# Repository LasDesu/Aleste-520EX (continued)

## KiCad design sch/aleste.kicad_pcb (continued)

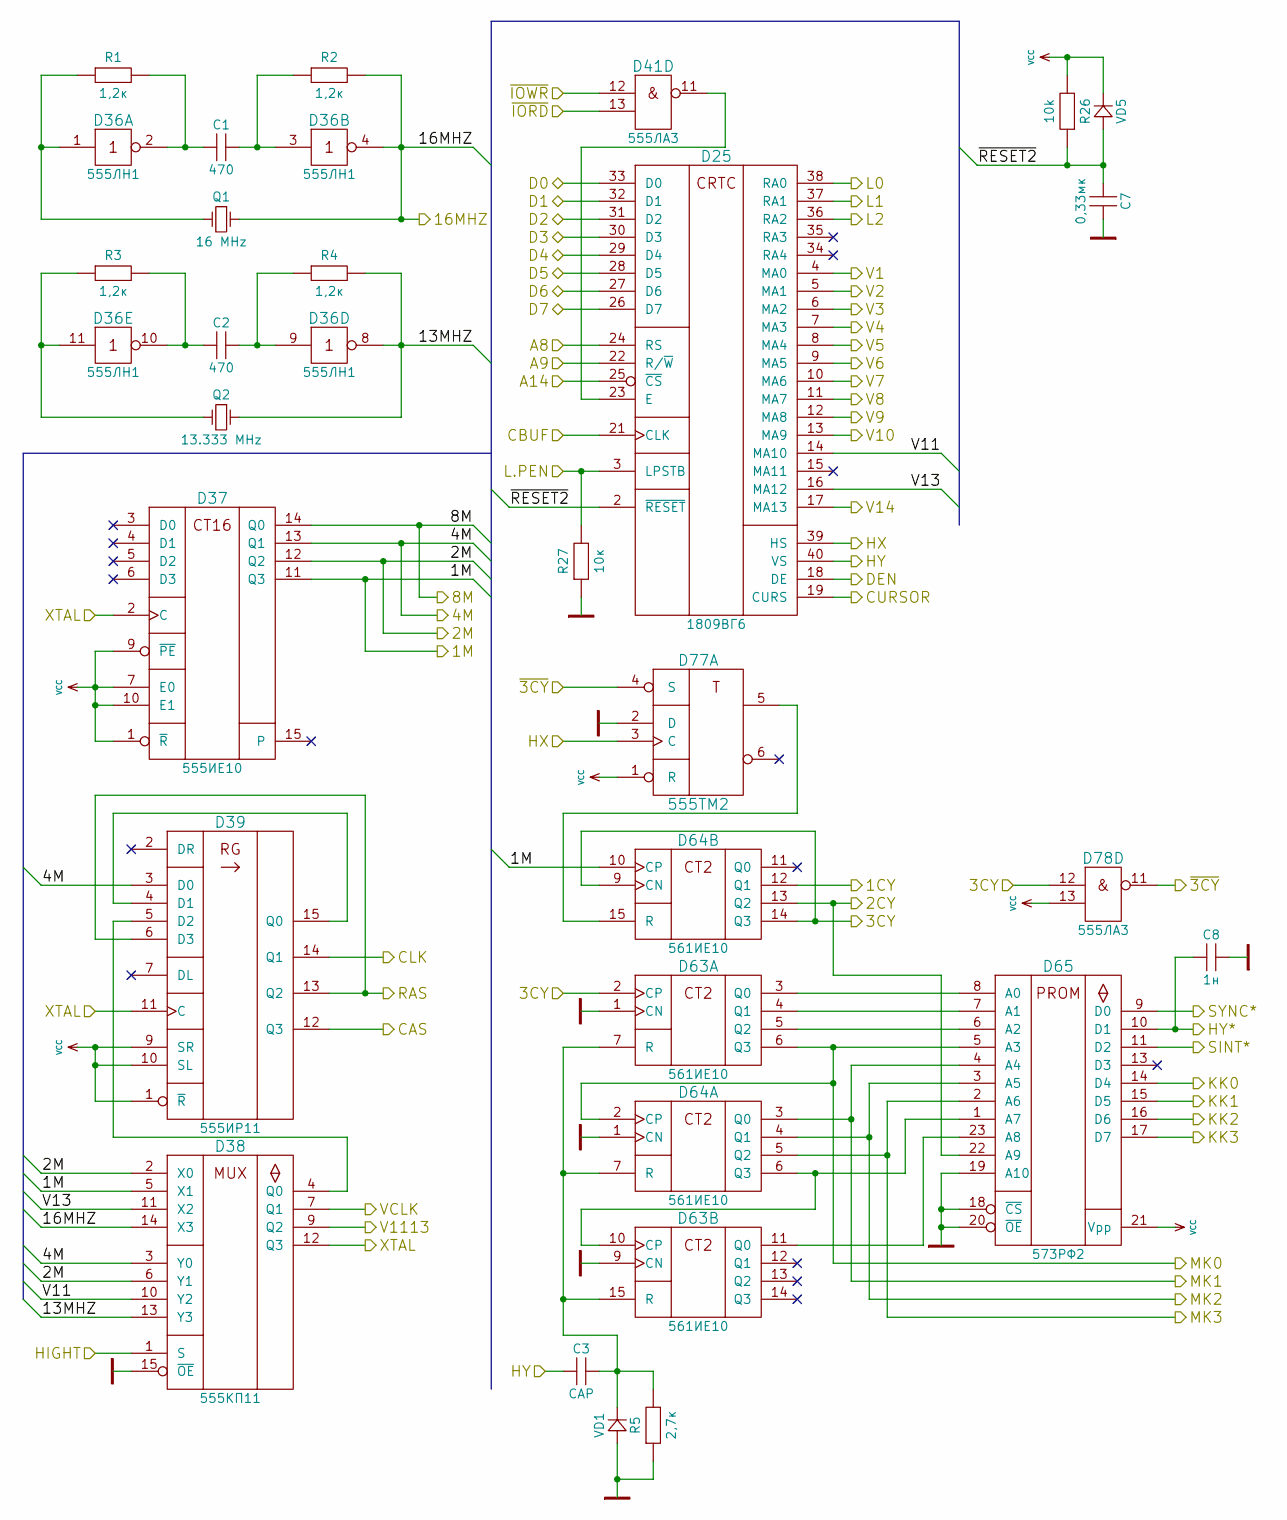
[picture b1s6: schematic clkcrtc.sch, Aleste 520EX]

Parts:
C1, C2: 470; C_Disc_D7.5_P2.5
C3: CAP; C_Disc_D7.5_P2.5
C7: 0,33мк; C_Disc_D7.5_P2.5
C8: 1н; C_Disc_D7.5_P2.5
D25: 1809ВГ6; DIP-40
D36: 555ЛН1; DIP-14
D37: 555ИЕ10; DIP-16
D38: 555КП11; DIP-16
D39: 555ИР11; DIP-16
D41, D78: 555ЛА3; DIP-14
D63, D64: 561ИЕ10; DIP-16
D65: 573РФ2; DIP-24
D77: 555ТМ2; DIP-14
Q1: 16 MHz; Crystal_HC49-U_Horizontal_Typ1
Q2: 13.333 MHz; Crystal_HC49-U_Horizontal_Typ1
R1, R2, R3, R4: 1,2к; Resistor_Horizontal_RM7.5mm
R5: 2,7к; Resistor_Horizontal_RM7.5mm
R26: 10k; Resistor_Horizontal_RM7.5mm
R27: 10к; Resistor_Horizontal_RM7.5mm
VD1, VD5: DIODE_MY; Diode_DO-35_SOD27_Horizontal_RM7.5

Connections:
/1CY: D64.12 (Q1); also elsewhere on the board
/1M: D37.11 (Q3), D38.5 (X1), D64.10 (CP); also elsewhere on the board
/2CY: D64.13 (Q2), D65.22 (A9); also elsewhere on the board
/2M: D37.12 (Q2), D38.2 (X0), D38.6 (Y1); also elsewhere on the board
/3CY: D63.2 (CP), D64.9 (CN), D64.14 (Q3), D78.12 (in1)
/4M: D37.13 (Q1), D38.3 (Y0), D39.3 (D0); also elsewhere on the board
/8M: D37.14 (Q0); also elsewhere on the board
/16MHZ: D36.4 (out), D38.14 (X3), Q1.1, R2.2; also elsewhere on the board
/A8: D25.24 (RS); also elsewhere on the board
/A9: D25.22 (R/~W); also elsewhere on the board
/A14: D25.25 (~CS); also elsewhere on the board
/CAS: D39.12 (Q3); also elsewhere on the board
/CBUF: D25.21 (CLK); also elsewhere on the board
/CLK: D39.14 (Q1); also elsewhere on the board
/CURSOR: D25.19 (CURS); also elsewhere on the board
/Clocks & CRTC/13MHZ: D36.8 (out), D38.13 (Y3), Q2.1, R4.2
/Clocks & CRTC/V11: D25.14 (MA10), D38.10 (Y2)
/Clocks & CRTC/V13: D25.16 (MA12), D38.11 (X2)
/Clocks & CRTC/~RESET2: C7.2, D25.2 (~RESET), R26.1, VD5.2
/D0: D25.33 (D0); also elsewhere on the board
/D1: D25.32 (D1); also elsewhere on the board
/D2: D25.31 (D2); also elsewhere on the board
/D3: D25.30 (D3); also elsewhere on the board
/D4: D25.29 (D4); also elsewhere on the board
/D5: D25.28 (D5); also elsewhere on the board
/D6: D25.27 (D6); also elsewhere on the board
/D7: D25.26 (D7); also elsewhere on the board
/DEN: D25.18 (DE); also elsewhere on the board
/HIGHT: D38.1 (S); also elsewhere on the board
/HX: D25.39 (HS), D77.3 (C); also elsewhere on the board
/HY: C3.1, D25.40 (VS); also elsewhere on the board
/HY*: C8.1, D65.10 (D1); also elsewhere on the board
/KK0: D65.14 (D4); also elsewhere on the board
/KK1: D65.15 (D5); also elsewhere on the board
/KK2: D65.16 (D6); also elsewhere on the board
/KK3: D65.17 (D7); also elsewhere on the board
/L0: D25.38 (RA0); also elsewhere on the board
/L1: D25.37 (RA1); also elsewhere on the board
/L2: D25.36 (RA2); also elsewhere on the board
/L.PEN: D25.3 (LPSTB), R27.2; also elsewhere on the board
/MK0: D63.6 (Q3), D64.2 (CP), D65.5 (A3); also elsewhere on the board
/MK1: D64.3 (Q0), D65.4 (A4); also elsewhere on the board
/MK2: D64.4 (Q1), D65.3 (A5); also elsewhere on the board
/MK3: D64.5 (Q2), D65.2 (A6); also elsewhere on the board
/RAS: D39.6 (D3), D39.13 (Q2); also elsewhere on the board
/SINT*: D65.11 (D2); also elsewhere on the board
/SYNC*: D65.9 (D0); also elsewhere on the board
/V1: D25.4 (MA0); also elsewhere on the board
/V2: D25.5 (MA1); also elsewhere on the board
/V3: D25.6 (MA2); also elsewhere on the board
/V4: D25.7 (MA3); also elsewhere on the board
/V5: D25.8 (MA4); also elsewhere on the board
/V6: D25.9 (MA5); also elsewhere on the board
/V7: D25.10 (MA6); also elsewhere on the board
/V8: D25.11 (MA7); also elsewhere on the board
/V9: D25.12 (MA8); also elsewhere on the board
/V10: D25.13 (MA9); also elsewhere on the board
/V14: D25.17 (MA13); also elsewhere on the board
/V1113: D38.9 (Q2); also elsewhere on the board
/VCLK: D38.7 (Q1); also elsewhere on the board
/XTAL: D37.2 (C), D38.12 (Q3), D39.11 (C); also elsewhere on the board
/~3CY: D77.4 (S), D78.11 (out); also elsewhere on the board
/~IORD: D41.13 (in2); also elsewhere on the board
/~IOWR: D41.12 (in1); also elsewhere on the board
GND: C7.1, C8.2, D25.1 (GND), D36.7 (GND), D37.8 (GND), D38.8 (GND), D38.15 (~OE), D39.8 (GND), D41.7 (GND), D63.1 (CN), D63.8 (GND), D63.9 (CN), D64.1 (CN), D64.8 (GND), D65.12 (GND), D65.18 (~CS), D65.19 (A10), D65.20 (~OE), D77.2 (D), D77.7 (GND), D78.7 (GND), R5.1, R27.1, VD1.2; also elsewhere on the board
unnamed: C1.1, D36.2 (out), R1.2
unnamed: C1.2, D36.3 (in), R2.1
unnamed: C2.1, D36.10 (out), R3.2
unnamed: C2.2, D36.9 (in), R4.1
unnamed: C3.2, D63.7 (R), D63.15 (R), D64.7 (R), R5.2, VD1.1
unnamed: D25.23 (E), D41.11 (out)
unnamed: D36.1 (in), Q1.2, R1.1
unnamed: D36.11 (in), Q2.2, R3.1
unnamed: D38.4 (Q0), D39.5 (D2)
unnamed: D39.4 (D1), D39.15 (Q0)
unnamed: D63.3 (Q0), D65.8 (A0)
unnamed: D63.4 (Q1), D65.7 (A1)
unnamed: D63.5 (Q2), D65.6 (A2)
unnamed: D63.10 (CP), D64.6 (Q3), D65.1 (A7)
unnamed: D63.11 (Q0), D65.23 (A8)
unnamed: D64.15 (R), D77.5
VCC: D25.20 (VCC), D36.14 (VCC), D37.1 (~R), D37.7 (E0), D37.9 (~PE), D37.10 (E1), D37.16 (VCC), D38.16 (VCC), D39.1 (~R), D39.9 (SR), D39.10 (SL), D39.16 (VCC), D41.14 (VCC), D63.16 (VCC), D64.16 (VCC), D65.21 (Vpp), D65.24 (VCC), D77.1 (R), D77.14 (VCC), D78.13 (in2), D78.14 (VCC), R26.2, VD5.1; also elsewhere on the board

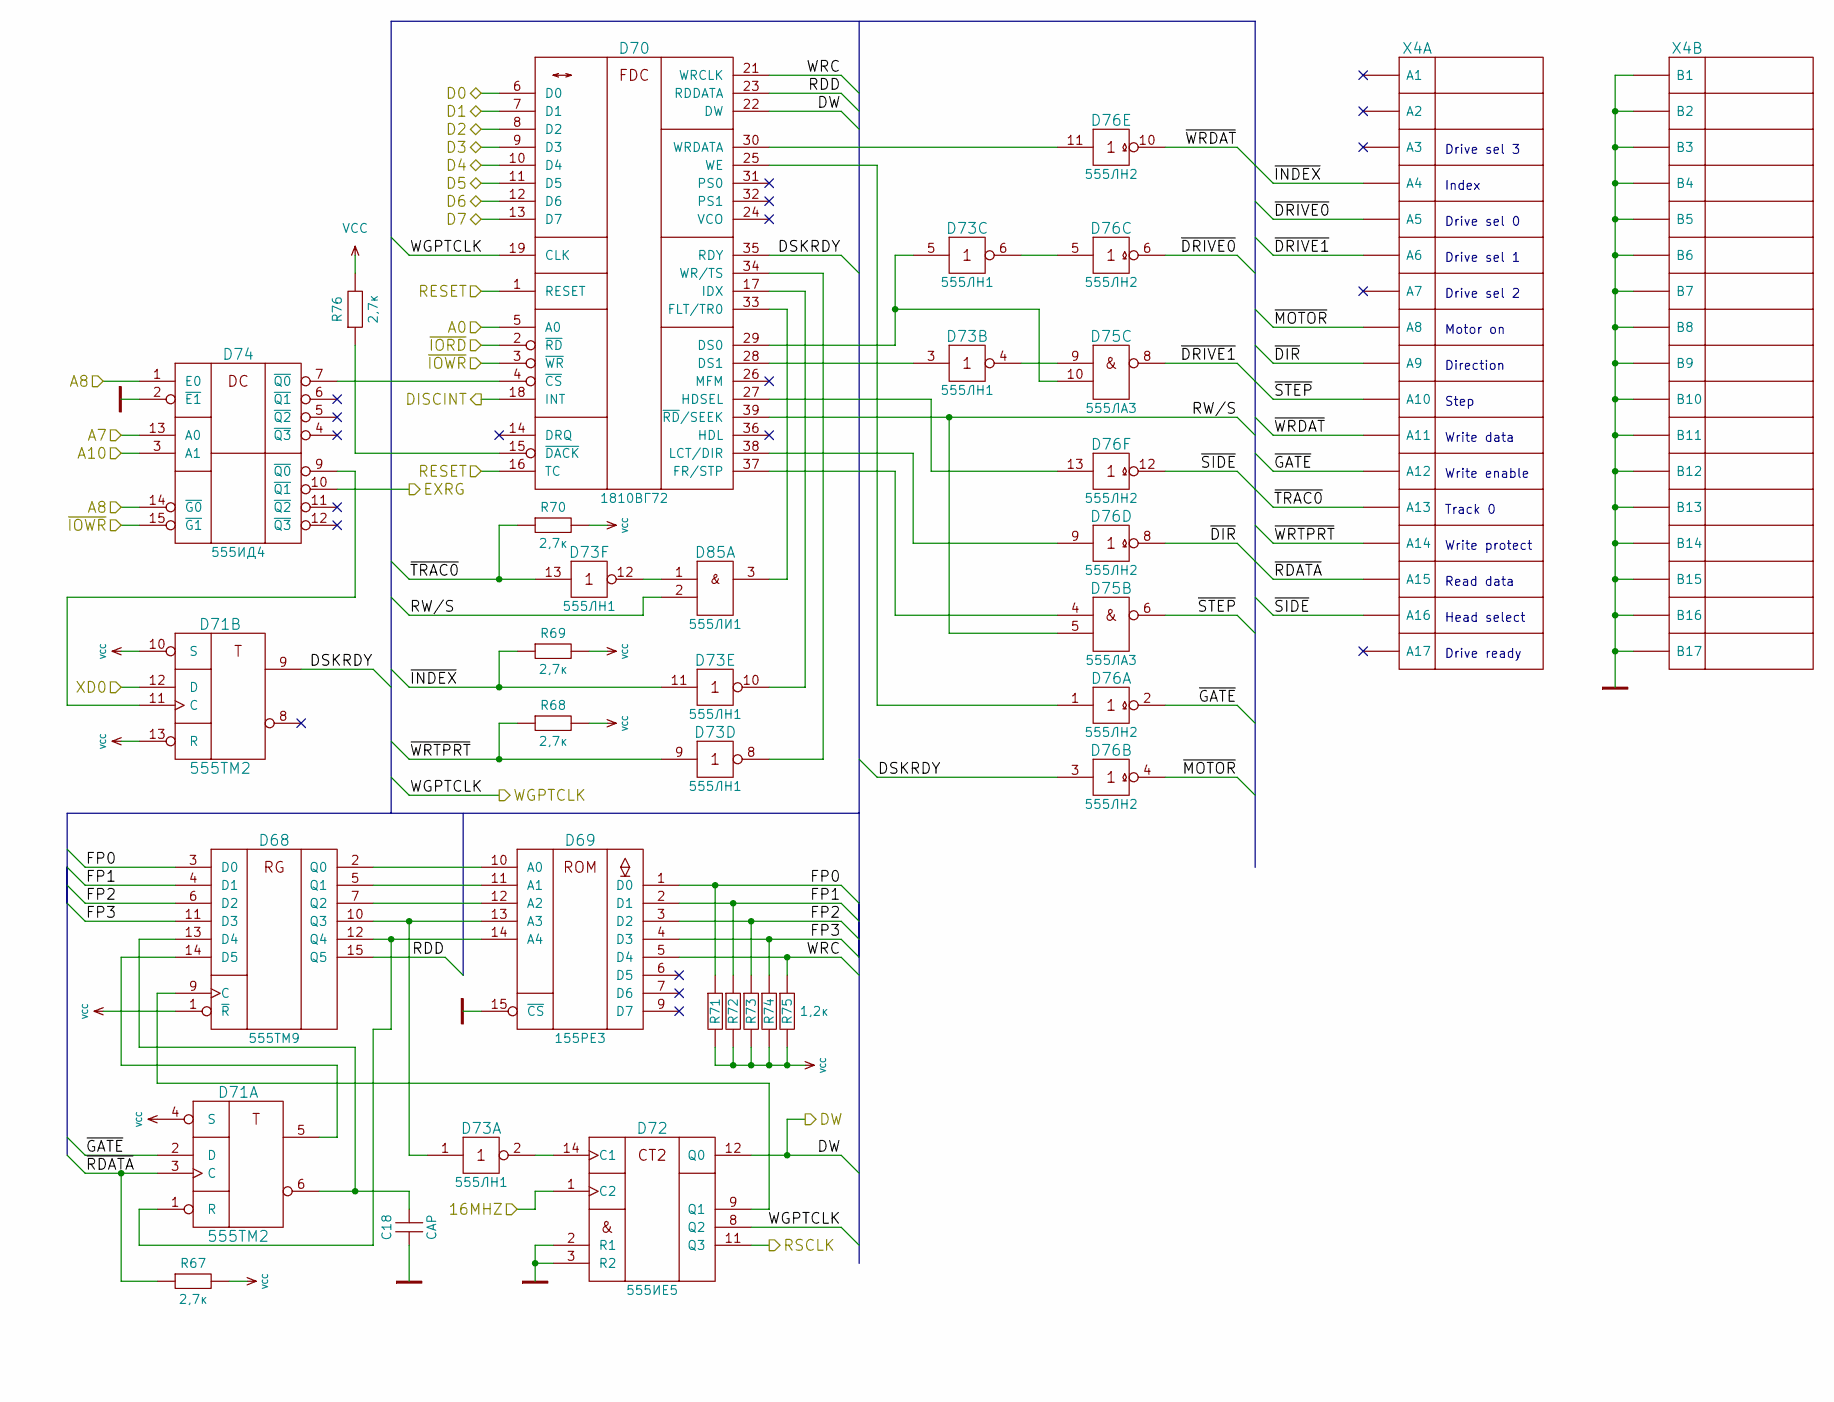
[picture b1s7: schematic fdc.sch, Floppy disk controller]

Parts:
C18: CAP; C_Disc_D7.5_P2.5
D68: 555ТМ9; DIP-16
D69: 155РЕ3; DIP-16
D70: 1810ВГ72; DIP-40
D71: 555ТМ2; DIP-14
D72: 555ИЕ5; DIP-14
D73: 555ЛН1; DIP-14
D74: 555ИД4; DIP-16
D75: 555ЛА3; DIP-14
D76: 555ЛН2; DIP-14
D85: 555ЛИ1; DIP-14
R67, R68, R69, R70: 2,7к; Resistor_Vertical_RM2.5mm
R71, R72, R73, R74, R75: 1,2к; Resistor_Vertical_RM2.5mm
R76: 2,7к; Resistor_Horizontal_RM7.5mm
X4: SLOT-34

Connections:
/16MHZ: D72.1 (C2); also elsewhere on the board
/A0: D70.5 (A0); also elsewhere on the board
/A7: D74.13 (A0); also elsewhere on the board
/A8: D74.1 (E0), D74.14 (~G0); also elsewhere on the board
/A10: D74.3 (A1); also elsewhere on the board
/D0: D70.6 (D0); also elsewhere on the board
/D1: D70.7 (D1); also elsewhere on the board
/D2: D70.8 (D2); also elsewhere on the board
/D3: D70.9 (D3); also elsewhere on the board
/D4: D70.10 (D4); also elsewhere on the board
/D5: D70.11 (D5); also elsewhere on the board
/D6: D70.12 (D6); also elsewhere on the board
/D7: D70.13 (D7); also elsewhere on the board
/DISCINT: D70.18 (INT); also elsewhere on the board
/DW: D70.22 (DW), D72.12 (Q0); also elsewhere on the board
/EXRG: D74.10 (~Q1); also elsewhere on the board
/FDC/DSKRDY: D70.35 (RDY), D71.9, D76.3 (in)
/FDC/FP0: D68.3 (D0), D69.1 (D0), R71.1
/FDC/FP1: D68.4 (D1), D69.2 (D1), R72.1
/FDC/FP2: D68.6 (D2), D69.3 (D2), R73.1
/FDC/FP3: D68.11 (D3), D69.4 (D3), R74.1
/FDC/RDD: D68.15 (Q5), D70.23 (RDDATA)
/FDC/RW/S: D70.39 (~RD~/SEEK), D75.5 (in2), D85.2 (in2)
/FDC/WRC: D69.5 (D4), D70.21 (WRCLK), R75.1
/FDC/~DIR: D76.8 (out), X4.A9
/FDC/~DRIVE0: D76.6 (out), X4.A5
/FDC/~DRIVE1: D75.8 (out), X4.A6
/FDC/~GATE: D71.2 (D), D76.2 (out), X4.A12
/FDC/~INDEX: D73.11 (in), R69.1, X4.A4
/FDC/~MOTOR: D76.4 (out), X4.A8
/FDC/~RDATA: D71.3 (C), R67.1, X4.A15
/FDC/~SIDE: D76.12 (out), X4.A16
/FDC/~STEP: D75.6 (out), X4.A10
/FDC/~TRAC0: D73.13 (in), R70.1, X4.A13
/FDC/~WRDAT: D76.10 (out), X4.A11
/FDC/~WRTPRT: D73.9 (in), R68.1, X4.A14
/RESET: D70.1 (RESET), D70.16 (TC); also elsewhere on the board
/RSCLK: D72.11 (Q3); also elsewhere on the board
/WGPTCLK: D70.19 (CLK), D72.8 (Q2); also elsewhere on the board
/XD0: D71.12 (D); also elsewhere on the board
/~IORD: D70.2 (~RD); also elsewhere on the board
/~IOWR: D70.3 (~WR), D74.15 (~G1); also elsewhere on the board
GND: C18.1, D68.8 (GND), D69.8 (GND), D69.15 (~CS), D70.20 (GND), D71.7 (GND), D72.2 (R1), D72.3 (R2), D72.10 (GND), D73.7 (GND), D74.2 (~E1), D74.8 (GND), D75.7 (GND), D76.7 (GND), D85.7 (GND), X4.B1, X4.B2, X4.B3, X4.B4, X4.B5, X4.B6, X4.B7, X4.B8, X4.B9, X4.B10, X4.B11, X4.B12, X4.B13, X4.B14 (B14~), X4.B15, X4.B16, X4.B17; also elsewhere on the board
unnamed: C18.2, D68.13 (D4), D71.6
unnamed: D68.2 (Q0), D69.10 (A0)
unnamed: D68.5 (Q1), D69.11 (A1)
unnamed: D68.7 (Q2), D69.12 (A2)
unnamed: D68.9 (C), D72.9 (Q1)
unnamed: D68.10 (Q3), D69.13 (A3), D73.1 (in)
unnamed: D68.12 (Q4), D69.14 (A4), D71.1 (R)
unnamed: D68.14 (D5), D71.5
unnamed: D70.4 (~CS), D74.7 (~Q0)
unnamed: D70.15 (~DACK), R76.1
unnamed: D70.17 (IDX), D73.10 (out)
unnamed: D70.25 (WE), D76.1 (in)
unnamed: D70.27 (HDSEL), D76.13 (in)
unnamed: D70.28 (DS1), D73.3 (in)
unnamed: D70.29 (DS0), D73.5 (in), D75.10 (in2)
unnamed: D70.30 (WRDATA), D76.11 (in)
unnamed: D70.33 (FLT/TR0), D85.3 (out)
unnamed: D70.34 (WR/TS), D73.8 (out)
unnamed: D70.37 (FR/STP), D75.4 (in1)
unnamed: D70.38 (LCT/DIR), D76.9 (in)
unnamed: D71.11 (C), D74.9 (~Q0)
unnamed: D72.14 (C1), D73.2 (out)
unnamed: D73.4 (out), D75.9 (in1)
unnamed: D73.6 (out), D76.5 (in)
unnamed: D73.12 (out), D85.1 (in1)
VCC: D68.1 (~R), D68.16 (VCC), D69.16 (VCC), D70.40 (VCC), D71.4 (S), D71.10 (S), D71.13 (R), D71.14 (VCC), D72.5 (VCC), D73.14 (VCC), D74.16 (VCC), D75.14 (VCC), D76.14 (VCC), D85.14 (VCC), R67.2, R68.2, R69.2, R70.2, R71.2, R72.2, R73.2, R74.2, R75.2, R76.2; also elsewhere on the board

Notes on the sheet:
Index
Drive sel 0
Drive sel 1
Drive sel 2
Motor on
Direction
Step
Write data
Drive sel 3
Write enable
Track 0
Write protect
Read data
Head select
Drive ready

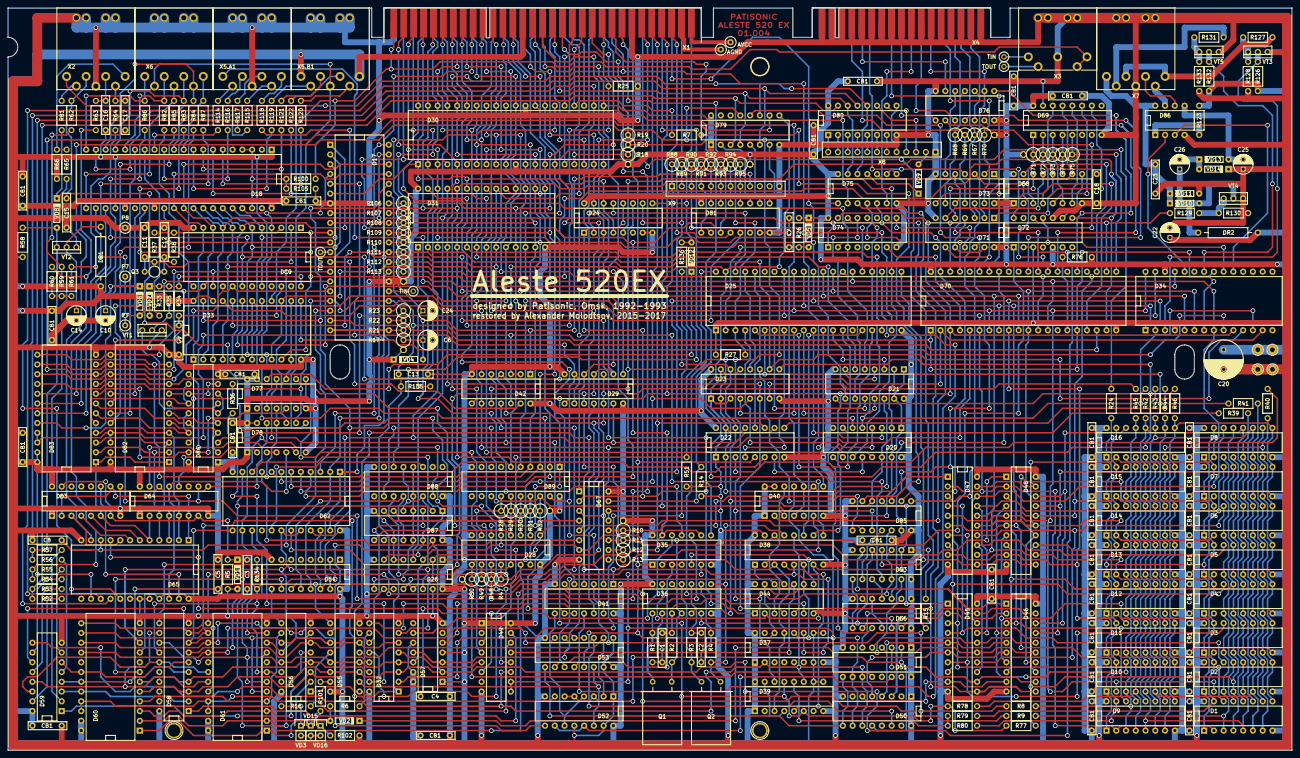
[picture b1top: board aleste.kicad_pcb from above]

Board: 2 copper layers, 328.8 x 190.0 mm, 315 parts (0 on the bottom side), 453 nets.

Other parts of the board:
CB1#2, CB1#3, CB1#4, CB1#5, CB1#6, CB1#7, CB1#8, CB1#9, CB1#10, CB1#11, CB1#12, CB1#13, CB1#14, CB1#15, CB1#16, CB1#17, CB1#18, CB1#19, CB1#20, CB1#21, CB1#22, CB1#23, CB1#24, CB1#25, CB1#26, CB1#27, CB1#28, CB1#29, CB1#30: CAP; C_Disc_D7.5_P2.5
P7#2: PIN

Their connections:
GND: CB1#2.1, CB1#3.1, CB1#4.1, CB1#5.1, CB1#6.1, CB1#7.1, CB1#8.1, CB1#9.1, CB1#10.1, CB1#11.1, CB1#12.1, CB1#13.1, CB1#14.1, CB1#15.1, CB1#16.1, CB1#17.1, CB1#18.1, CB1#19.1, CB1#20.1, CB1#21.1, CB1#22.1, CB1#23.1, CB1#24.1, CB1#25.1, CB1#26.1, CB1#27.1, CB1#28.1, CB1#29.1, CB1#30.1; also elsewhere on the board
unnamed 511: P7#2.1; also elsewhere on the board
VCC: CB1#2.2, CB1#3.2, CB1#4.2, CB1#5.2, CB1#6.2, CB1#7.2, CB1#8.2, CB1#9.2, CB1#10.2, CB1#11.2, CB1#12.2, CB1#13.2, CB1#14.2, CB1#15.2, CB1#16.2, CB1#17.2, CB1#18.2, CB1#19.2, CB1#20.2, CB1#21.2, CB1#22.2, CB1#23.2, CB1#24.2, CB1#25.2, CB1#26.2, CB1#27.2, CB1#28.2, CB1#29.2, CB1#30.2; also elsewhere on the board

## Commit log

2016-05-15 Initial commit. Almost everything is done.
2016-05-15 More precise version. PCB needs a lot of work.
2016-05-15 Start to move to a bit more affordable components
2016-06-03 Update IR22 and IR23 symbols
2016-06-26 IR22 and IR23 symbols updated, part values updated
2016-06-27 GAL based PLL for FDC
2016-08-30 Another ROM replaced with PLD, source included
2016-08-31 Palette update for new schematic
2016-12-07 Fix MVI signal
2016-12-07 Board fully redrawn
2017-01-02 C8 on its place
2017-01-03 Cosmetic board fixes
2017-01-03 Original board with all fixes
2017-01-03 Cosmetic schematic fix
2017-01-03 Fixed documentation
